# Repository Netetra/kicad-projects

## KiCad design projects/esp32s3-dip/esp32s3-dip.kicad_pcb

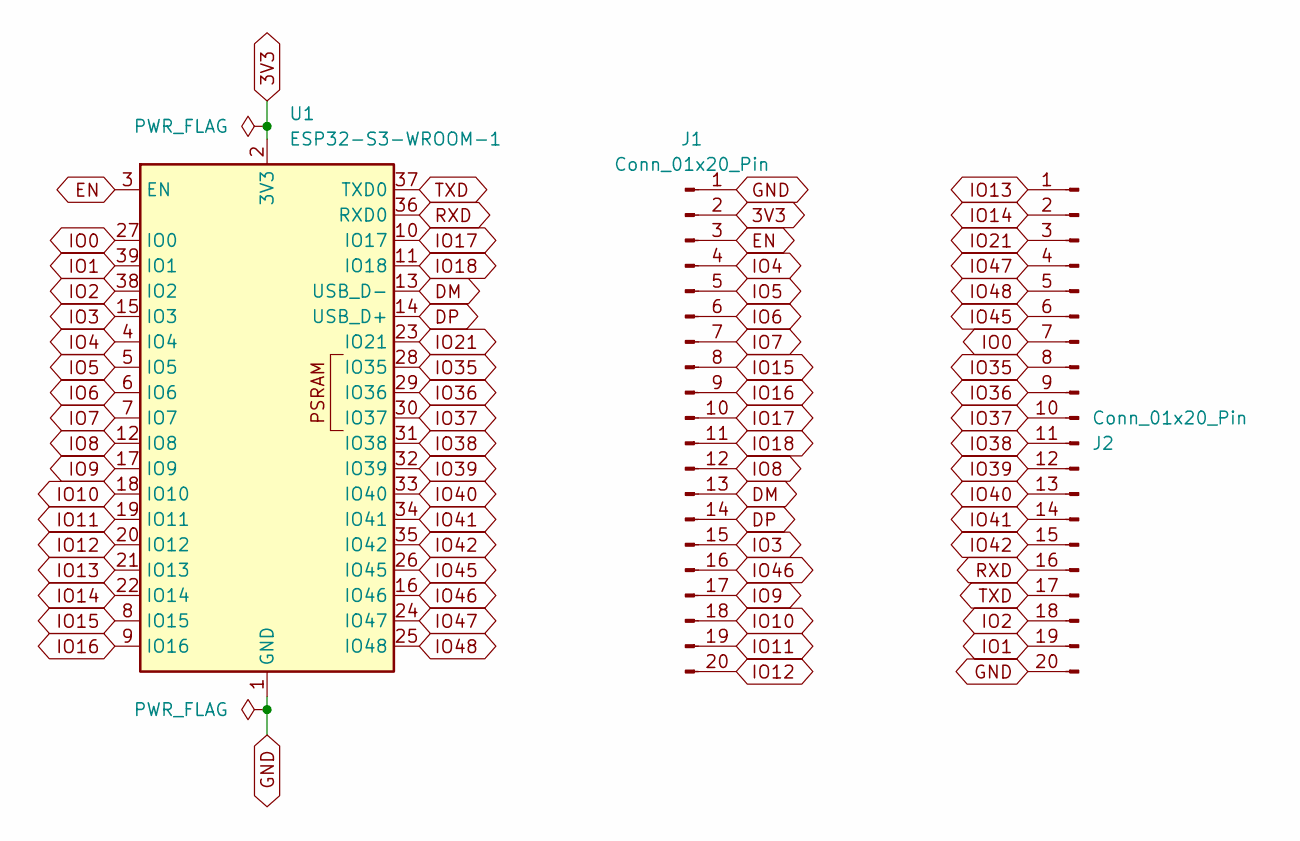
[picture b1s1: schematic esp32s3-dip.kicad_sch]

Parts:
J1, J2: Conn_01x20_Pin; PinHeader_1x20_P2.54mm_Vertical
U1: ESP32-S3-WROOM-1; ESP32-S3-WROOM-1U

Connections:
3V3: J1.2, U1.2 (3V3)
DM: J1.13, U1.13 (USB_D-)
DP: J1.14, U1.14 (USB_D+)
EN: J1.3, U1.3 (EN)
GND: J1.1, J2.20, U1.1 (GND), U1.40 (GND), U1.41 (GND)
IO0: J2.7, U1.27 (IO0)
IO1: J2.19, U1.39 (IO1)
IO2: J2.18, U1.38 (IO2)
IO3: J1.15, U1.15 (IO3)
IO4: J1.4, U1.4 (IO4)
IO5: J1.5, U1.5 (IO5)
IO6: J1.6, U1.6 (IO6)
IO7: J1.7, U1.7 (IO7)
IO8: J1.12, U1.12 (IO8)
IO9: J1.17, U1.17 (IO9)
IO10: J1.18, U1.18 (IO10)
IO11: J1.19, U1.19 (IO11)
IO12: J1.20, U1.20 (IO12)
IO13: J2.1, U1.21 (IO13)
IO14: J2.2, U1.22 (IO14)
IO15: J1.8, U1.8 (IO15)
IO16: J1.9, U1.9 (IO16)
IO17: J1.10, U1.10 (IO17)
IO18: J1.11, U1.11 (IO18)
IO21: J2.3, U1.23 (IO21)
IO35: J2.8, U1.28 (IO35)
IO36: J2.9, U1.29 (IO36)
IO37: J2.10, U1.30 (IO37)
IO38: J2.11, U1.31 (IO38)
IO39: J2.12, U1.32 (IO39)
IO40: J2.13, U1.33 (IO40)
IO41: J2.14, U1.34 (IO41)
IO42: J2.15, U1.35 (IO42)
IO45: J2.6, U1.26 (IO45)
IO46: J1.16, U1.16 (IO46)
IO47: J2.4, U1.24 (IO47)
IO48: J2.5, U1.25 (IO48)
RXD: J2.16, U1.36 (RXD0)
TXD: J2.17, U1.37 (TXD0)

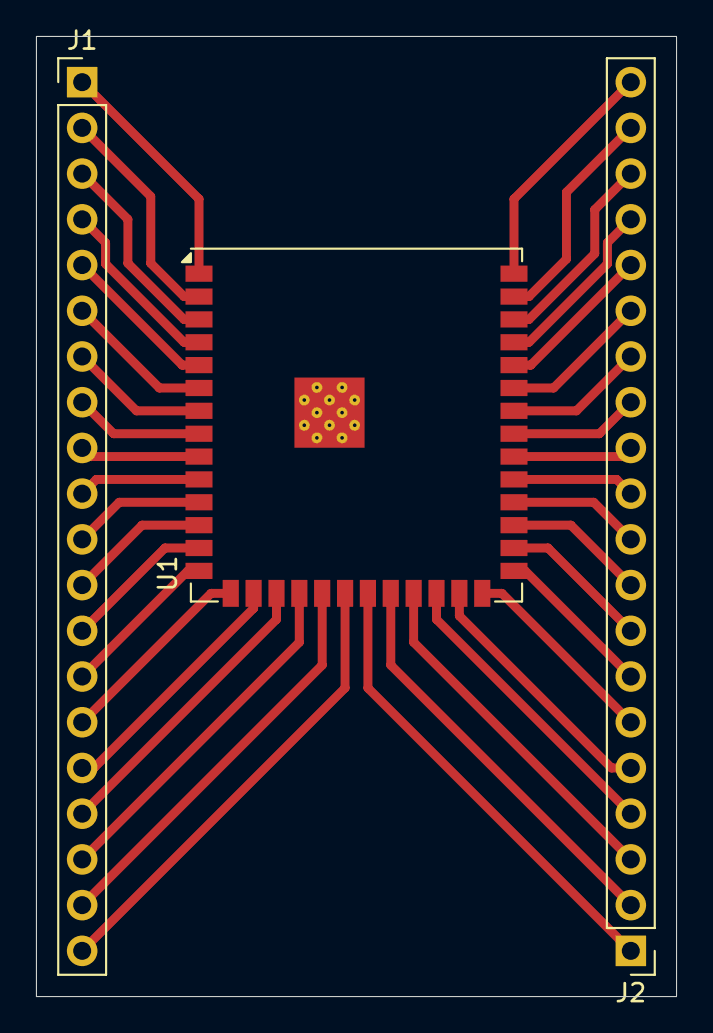
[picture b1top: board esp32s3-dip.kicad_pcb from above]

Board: 2 copper layers, 35.6 x 53.3 mm, 3 parts (0 on the bottom side), 39 nets.

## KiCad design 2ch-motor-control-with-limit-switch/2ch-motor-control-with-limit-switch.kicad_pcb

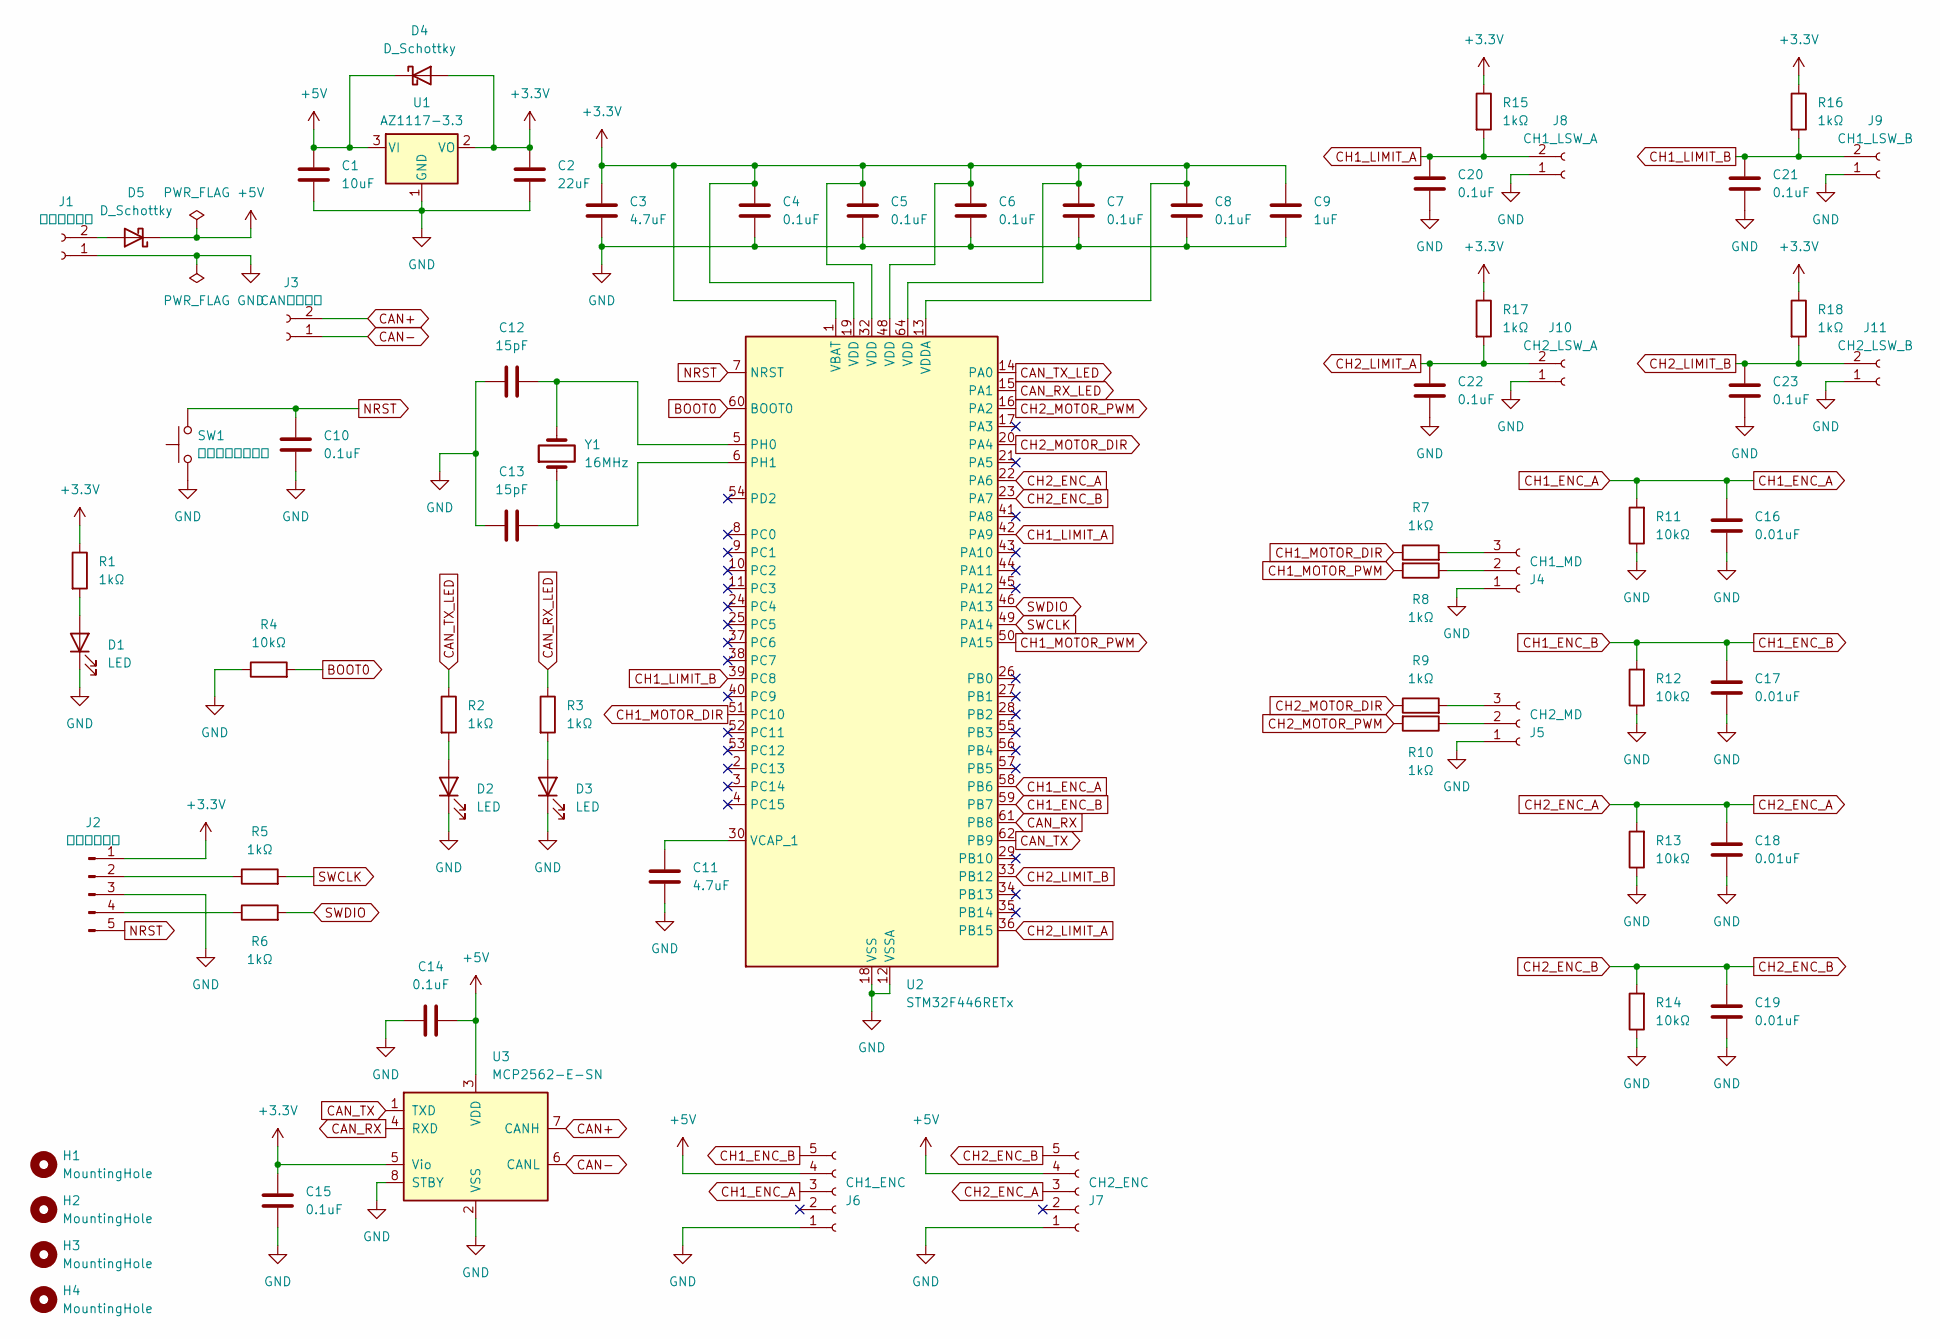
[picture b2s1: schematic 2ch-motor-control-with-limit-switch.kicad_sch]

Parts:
C1: 10uF; C_0603_1608Metric
C2: 22uF; C_0603_1608Metric
C3, C11: 4.7uF; C_0603_1608Metric
C4, C5, C6, C7, C8, C10, C14, C15, C20, C21, C22, C23: 0.1uF; C_0603_1608Metric
C9: 1uF; C_0603_1608Metric
C12, C13: 15pF; C_0603_1608Metric
C16, C17, C18, C19: 0.01uF; C_0603_1608Metric
D1, D2, D3: LED; LED_0603_1608Metric
D4, D5: D_Schottky; US2H
H1, H2, H3, H4: MountingHole; MountingHole_3.2mm_M3
J1: 電源コネクタ; AMASS_XT30PW-M_1x02_P2.50mm_Horizontal
J2: デバッグ端子; PinSocket_1x05_P2.54mm_Horizontal
J3: CANコネクタ; JST_XH_S2B-XH-A_1x02_P2.50mm_Horizontal
J4: CH1_MD; JST_XH_S3B-XH-A_1x03_P2.50mm_Horizontal
J5: CH2_MD; JST_XH_S3B-XH-A_1x03_P2.50mm_Horizontal
J6: CH1_ENC; JST_XH_S5B-XH-A_1x05_P2.50mm_Horizontal
J7: CH2_ENC; JST_XH_S5B-XH-A_1x05_P2.50mm_Horizontal
J8: CH1_LSW_A; JST_XH_S2B-XH-A_1x02_P2.50mm_Horizontal
J9: CH1_LSW_B; JST_XH_S2B-XH-A_1x02_P2.50mm_Horizontal
J10: CH2_LSW_A; JST_XH_S2B-XH-A_1x02_P2.50mm_Horizontal
J11: CH2_LSW_B; JST_XH_S2B-XH-A_1x02_P2.50mm_Horizontal
R1, R2, R3, R5, R6, R7, R8, R9, R10, R15, R16, R17, R18: 1kΩ; R_0603_1608Metric
R4, R11, R12, R13, R14: 10kΩ; R_0603_1608Metric
SW1: リセットスイッチ; SW_PUSH_6mm_H5mm
U1: AZ1117-3.3; SOT-223-3_TabPin2
U2: STM32F446RETx; LQFP-64_10x10mm_P0.5mm
U3: MCP2562-E-SN; SOIC-8_3.9x4.9mm_P1.27mm
Y1: 16MHz; Crystal_HC49-4H_Vertical

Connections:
+3.3V: C2.1, C3.1, C4.1, C5.1, C6.1, C7.1, C8.1, C9.1, C15.1, D4.2 (A), J2.1, R1.1, R15.1, R16.1, R17.1, R18.1, U1.2 (VO), U2.1 (VBAT), U2.13 (VDDA), U2.19 (VDD), U2.32 (VDD), U2.48 (VDD), U2.64 (VDD), U3.5 (Vio)
+5V: C1.1, C14.2, D4.1 (K), D5.1 (K), J6.4, J7.4, U1.3 (VI), U3.3 (VDD)
BOOT0: R4.2, U2.60 (BOOT0)
CAN+: J3.2, U3.7 (CANH)
CAN-: J3.1, U3.6 (CANL)
CAN_RX: U2.61 (PB8), U3.4 (RXD)
CAN_RX_LED: R3.1, U2.15 (PA1)
CAN_TX: U2.62 (PB9), U3.1 (TXD)
CAN_TX_LED: R2.1, U2.14 (PA0)
CH1_ENC_A: C16.1, J6.3, R11.2, U2.58 (PB6)
CH1_ENC_B: C17.1, J6.5, R12.2, U2.59 (PB7)
CH1_LIMIT_A: C20.1, J8.2, R15.2, U2.42 (PA9)
CH1_LIMIT_B: C21.1, J9.2, R16.2, U2.39 (PC8)
CH1_MOTOR_DIR: R7.1, U2.51 (PC10)
CH1_MOTOR_PWM: R8.2, U2.50 (PA15)
CH2_ENC_A: C18.1, J7.3, R13.2, U2.22 (PA6)
CH2_ENC_B: C19.1, J7.5, R14.2, U2.23 (PA7)
CH2_LIMIT_A: C22.1, J10.2, R17.2, U2.36 (PB15)
CH2_LIMIT_B: C23.1, J11.2, R18.2, U2.33 (PB12)
CH2_MOTOR_DIR: R9.1, U2.20 (PA4)
CH2_MOTOR_PWM: R10.2, U2.16 (PA2)
GND: C1.2, C2.2, C3.2, C4.2, C5.2, C6.2, C7.2, C8.2, C9.2, C10.2, C11.1, C12.1, C13.1, C14.1, C15.2, C16.2, C17.2, C18.2, C19.2, C20.2, C21.2, C22.2, C23.2, D1.1 (K), D2.1 (K), D3.1 (K), J1.1, J2.3, J4.1, J5.1, J6.1, J7.1, J8.1, J9.1, J10.1, J11.1, R4.1, R11.1, R12.1, R13.1, R14.1, SW1.1, U1.1 (GND), U2.12 (VSSA), U2.18 (VSS), U2.31 (VSS), U2.47 (VSS), U2.63 (VSS), U3.2 (VSS), U3.8 (STBY)
NRST: C10.1, J2.5, SW1.2, U2.7 (NRST)
unnamed: D1.2 (A), R1.2
unnamed: D2.2 (A), R2.2
unnamed: D3.2 (A), R3.2
unnamed: D5.2 (A), J1.2
unnamed: J2.2, R5.1
unnamed: J2.4, R6.1
unnamed: J4.2, R8.1
unnamed: J4.3, R7.2
unnamed: J5.2, R10.1
unnamed: J5.3, R9.2
unnamed: C12.2, U2.5 (PH0), Y1.2
unnamed: C13.2, U2.6 (PH1), Y1.1
unnamed: C11.2, U2.30 (VCAP_1)
SWCLK: R5.2, U2.49 (PA14)
SWDIO: R6.2, U2.46 (PA13)

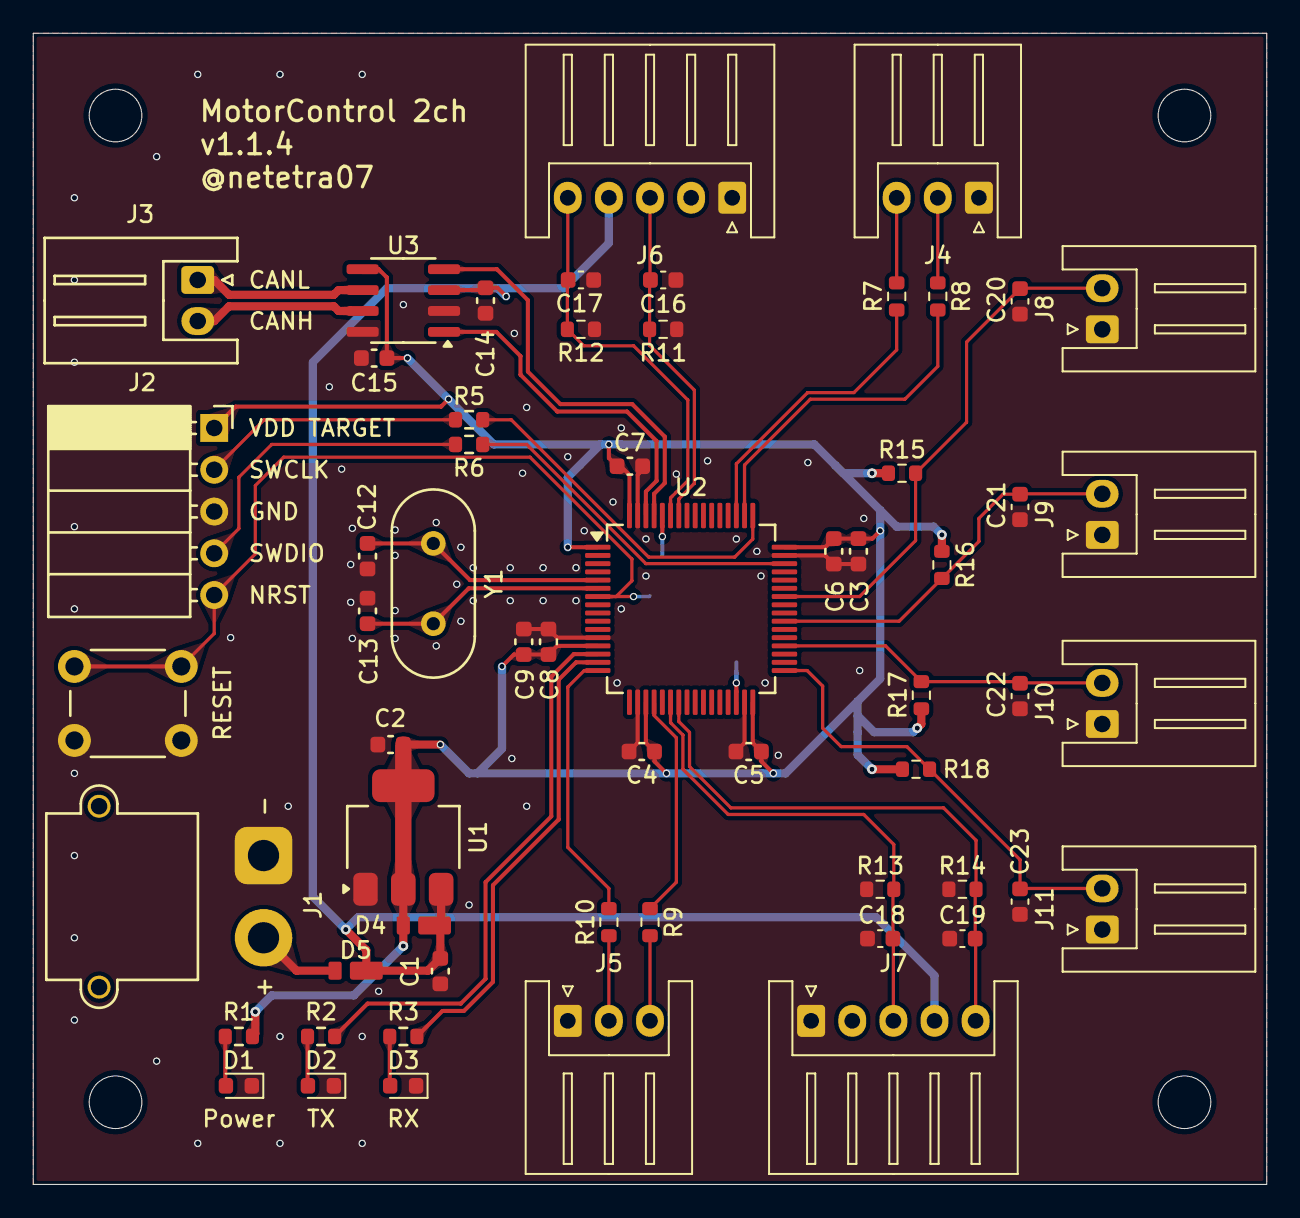
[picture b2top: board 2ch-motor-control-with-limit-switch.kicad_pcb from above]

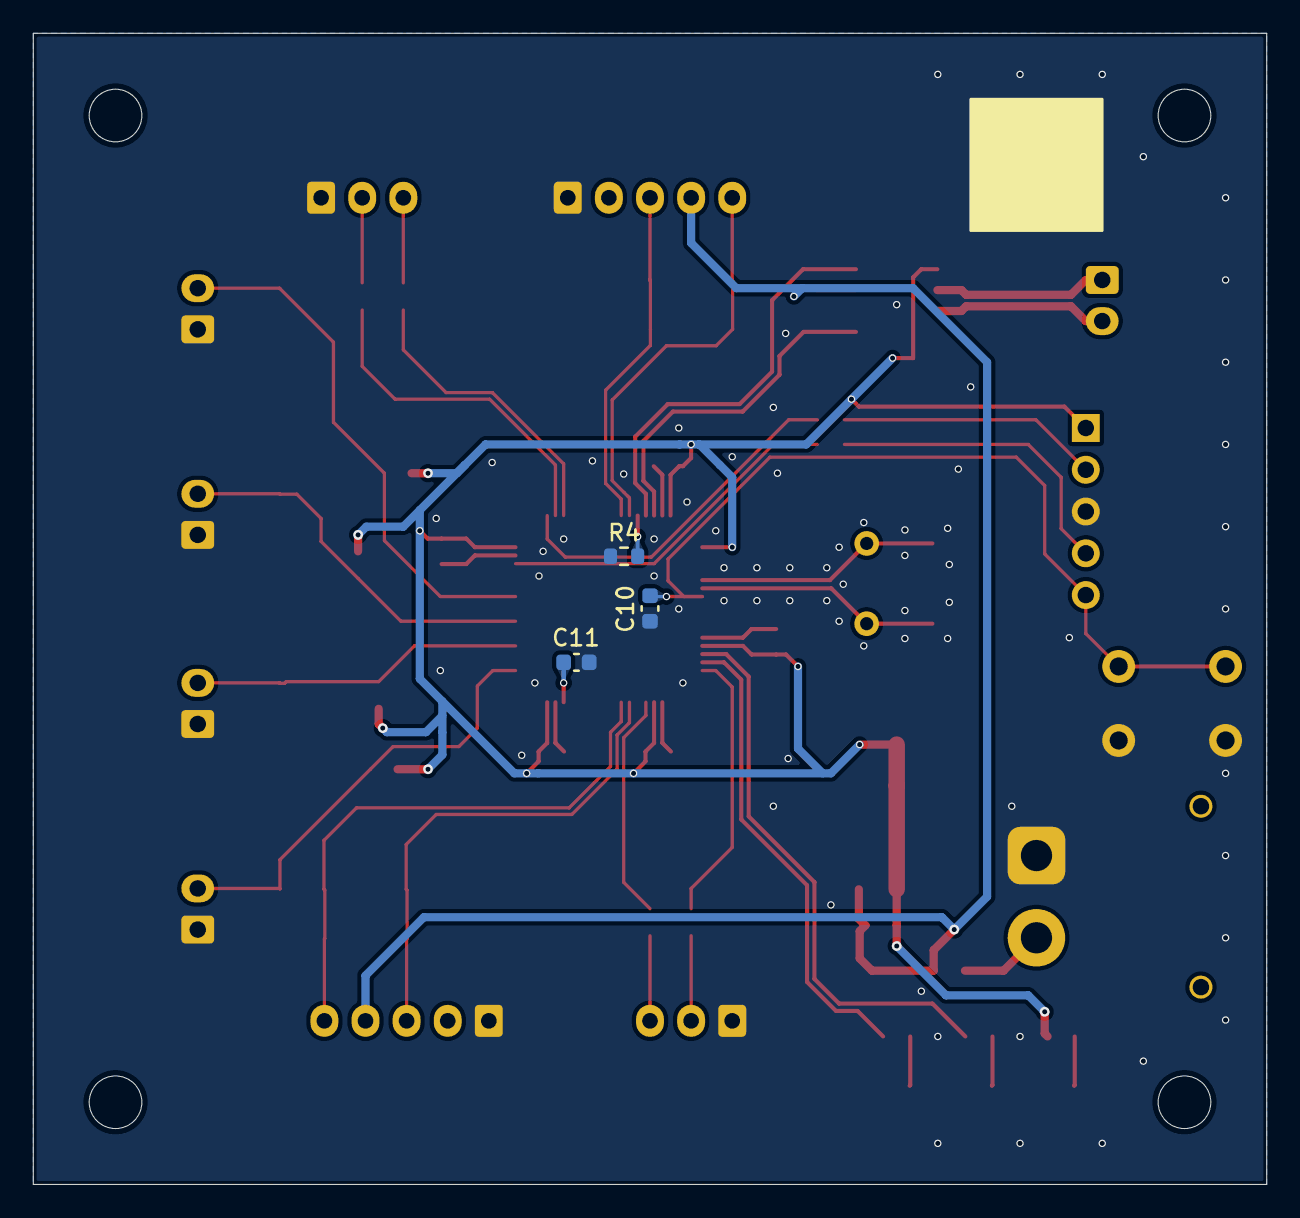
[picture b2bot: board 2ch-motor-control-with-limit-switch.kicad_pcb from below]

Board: 2 copper layers, 75.0 x 70.0 mm, 66 parts (3 on the bottom side), 38 nets.

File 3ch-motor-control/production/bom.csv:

Designator,Footprint,Quantity,Value,LCSC Part #
C1,0603,1,10uF,
"C10, C14, C15, C4, C5, C6, C7, C8",0603,8,0.1uF,
"C11, C3",0603,2,4.7uF,
"C12, C13",0603,2,15pF,
"C16, C17, C18, C19, C20, C21",0603,6,0.01uF,
C2,0603,1,22uF,
C9,0603,1,1uF,
"D1, D2, D3",0603,3,LED,
ENC1,JST_XH_S5B-XH-A_1x05_P2.50mm_Horizontal,1,CH1_ENC,
ENC2,JST_XH_S5B-XH-A_1x05_P2.50mm_Horizontal,1,CH2_ENC,
ENC3,JST_XH_S5B-XH-A_1x05_P2.50mm_Horizontal,1,CH3_ENC,
J1,AMASS_XT30PW-M_1x02_P2.50mm_Horizontal,1,電源コネクタ,
J2,PinSocket_1x05_P2.54mm_Horizontal,1,デバッグ端子,
J3,JST_XH_S2B-XH-A_1x02_P2.50mm_Horizontal,1,CANコネクタ,
MD1,JST_XH_S3B-XH-A_1x03_P2.50mm_Horizontal,1,CH1_MOTOR,
MD2,JST_XH_S3B-XH-A_1x03_P2.50mm_Horizontal,1,CH2_MOTOR,
MD3,JST_XH_S3B-XH-A_1x03_P2.50mm_Horizontal,1,CH3_MOTOR,
"R1, R10, R11, R12, R14, R16, R17, R18, R2, R20, R22, R23, R24, R3, R5, R6, R8",0603,17,1kΩ,
"R13, R15, R19, R21, R4, R7, R9",0603,7,10kΩ,
SW1,SW_PUSH_6mm_H5mm,1,リセットスイッチ,
U1,SOT-223-3_TabPin2,1,AZ1117-3.3,
U2,LQFP-64_10x10mm_P0.5mm,1,STM32F446RETx,
U3,SOIC-8_3.9x4.9mm_P1.27mm,1,MCP2562-E-SN,
Y1,Crystal_HC49-4H_Vertical,1,16MHz,

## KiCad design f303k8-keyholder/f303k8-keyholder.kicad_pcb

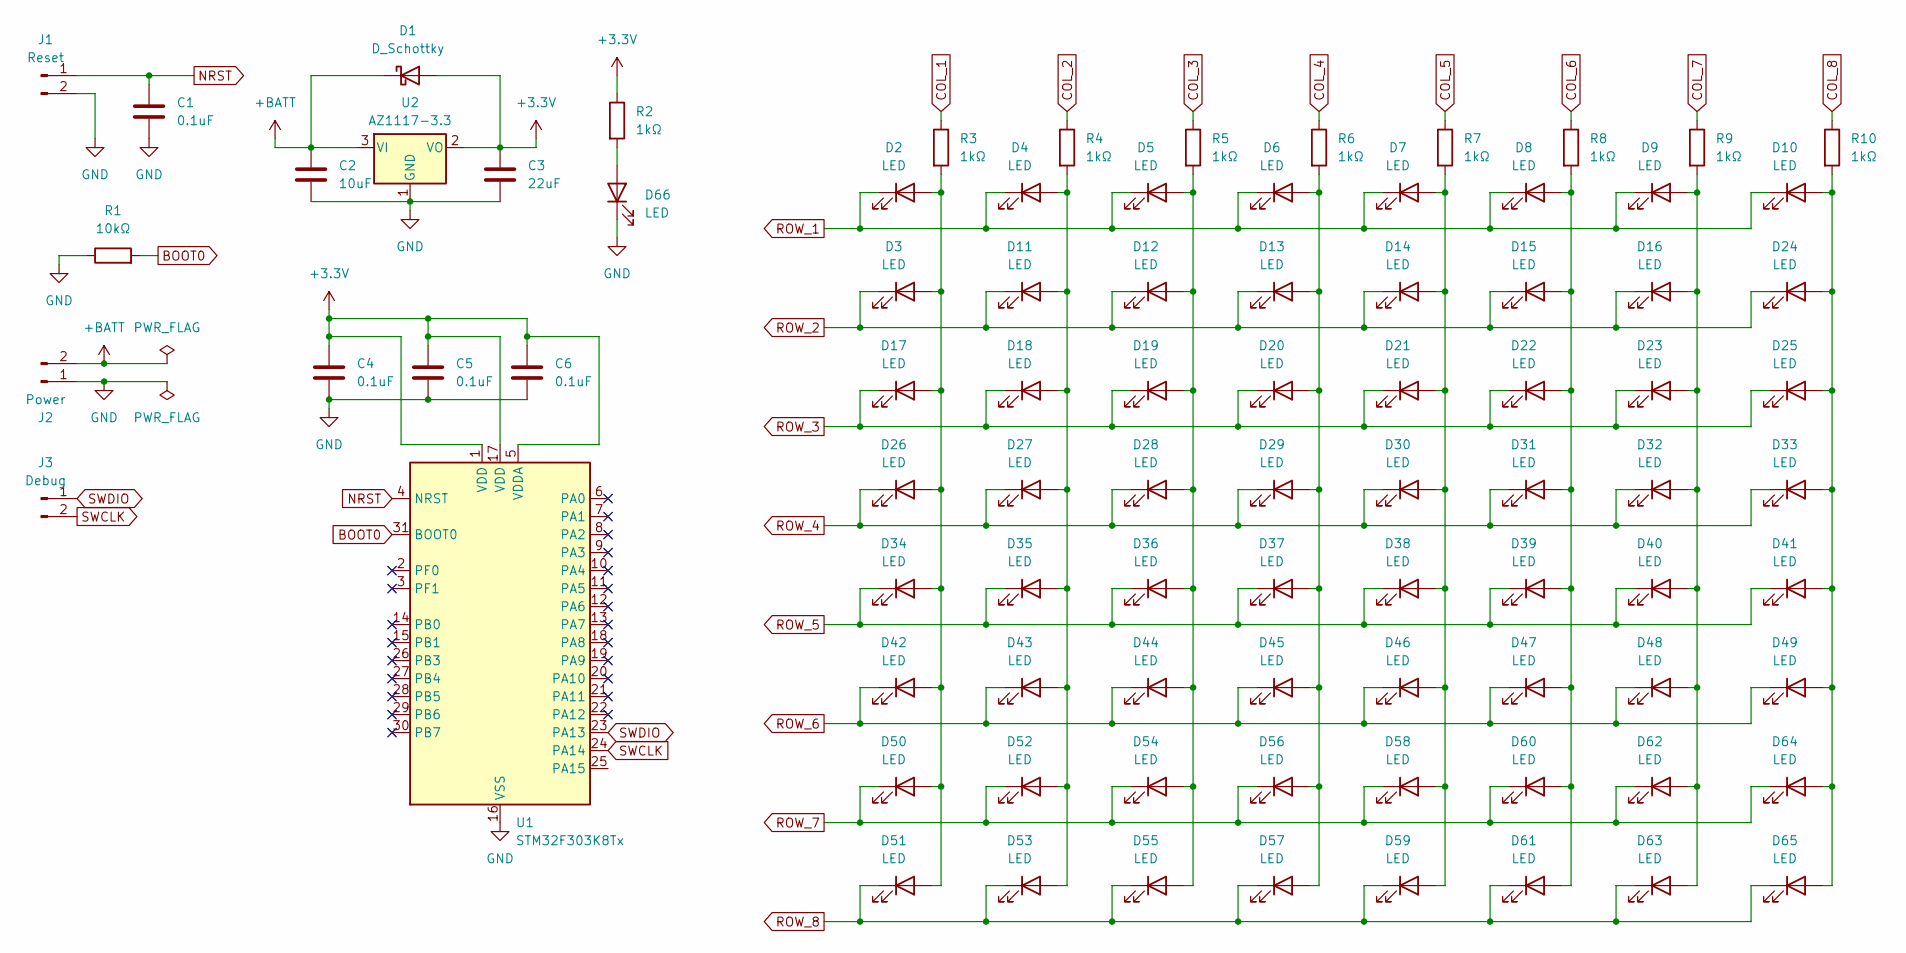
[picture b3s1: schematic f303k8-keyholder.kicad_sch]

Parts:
C1, C4, C5, C6: 0.1uF; C_0603_1608Metric
C2: 10uF; C_0603_1608Metric
C3: 22uF; C_0603_1608Metric
D1: D_Schottky; US2H
D2, D3, D4, D5, D6, D7, D8, D9, D10, D11, D12, D13, D14, D15, D16, D17, D18, D19, D20, D21, D22, D23, D24, D25, D26, D27, D28, D29, D30, D31, D32, D33, D34, D35, D36, D37, D38, D39, D40, D41, D42, D43, D44, D45, D46, D47, D48, D49, D50, D51, D52, D53, D54, D55, D56, D57, D58, D59, D60, D61, D62, D63, D64, D65, D66: LED; LED_0603_1608Metric
J1: Reset; PinHeader_1x02_P1.00mm_Vertical
J2: Power; PinSocket_1x02_P2.54mm_Horizontal
J3: Debug; PinHeader_1x02_P1.00mm_Vertical
R1: 10kΩ; R_0603_1608Metric
R2, R3, R4, R5, R6, R7, R8, R9, R10: 1kΩ; R_0603_1608Metric
U1: STM32F303K8Tx; LQFP-32_7x7mm_P0.8mm
U2: AZ1117-3.3; SOT-223-3_TabPin2

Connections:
+3.3V: C3.1, C4.1, C5.1, C6.1, D1.2 (A), R2.1, U1.1 (VDD), U1.5 (VDDA), U1.17 (VDD), U2.2 (VO)
+BATT: C2.1, D1.1 (K), J2.2, U2.3 (VI)
BOOT0: R1.2, U1.31 (BOOT0)
COL_1: R3.1
COL_2: R4.1
COL_3: R5.1
COL_4: R6.1
COL_5: R7.1
COL_6: R8.1
COL_7: R9.1
COL_8: R10.1
GND: C1.2, C2.2, C3.2, C4.2, C5.2, C6.2, D66.1 (K), J1.2, J2.1, R1.1, U1.16 (VSS), U1.32 (VSS), U2.1 (GND)
NRST: C1.1, J1.1, U1.4 (NRST)
unnamed: D10.2 (A), D24.2 (A), D25.2 (A), D33.2 (A), D41.2 (A), D49.2 (A), D64.2 (A), D65.2 (A), R10.2
unnamed: D4.2 (A), D11.2 (A), D18.2 (A), D27.2 (A), D35.2 (A), D43.2 (A), D52.2 (A), D53.2 (A), R4.2
unnamed: D5.2 (A), D12.2 (A), D19.2 (A), D28.2 (A), D36.2 (A), D44.2 (A), D54.2 (A), D55.2 (A), R5.2
unnamed: D6.2 (A), D13.2 (A), D20.2 (A), D29.2 (A), D37.2 (A), D45.2 (A), D56.2 (A), D57.2 (A), R6.2
unnamed: D7.2 (A), D14.2 (A), D21.2 (A), D30.2 (A), D38.2 (A), D46.2 (A), D58.2 (A), D59.2 (A), R7.2
unnamed: D8.2 (A), D15.2 (A), D22.2 (A), D31.2 (A), D39.2 (A), D47.2 (A), D60.2 (A), D61.2 (A), R8.2
unnamed: D9.2 (A), D16.2 (A), D23.2 (A), D32.2 (A), D40.2 (A), D48.2 (A), D62.2 (A), D63.2 (A), R9.2
unnamed: D2.2 (A), D3.2 (A), D17.2 (A), D26.2 (A), D34.2 (A), D42.2 (A), D50.2 (A), D51.2 (A), R3.2
unnamed: D66.2 (A), R2.2
ROW_1: D2.1 (K), D4.1 (K), D5.1 (K), D6.1 (K), D7.1 (K), D8.1 (K), D9.1 (K), D10.1 (K)
ROW_2: D3.1 (K), D11.1 (K), D12.1 (K), D13.1 (K), D14.1 (K), D15.1 (K), D16.1 (K), D24.1 (K)
ROW_3: D17.1 (K), D18.1 (K), D19.1 (K), D20.1 (K), D21.1 (K), D22.1 (K), D23.1 (K), D25.1 (K)
ROW_4: D26.1 (K), D27.1 (K), D28.1 (K), D29.1 (K), D30.1 (K), D31.1 (K), D32.1 (K), D33.1 (K)
ROW_5: D34.1 (K), D35.1 (K), D36.1 (K), D37.1 (K), D38.1 (K), D39.1 (K), D40.1 (K), D41.1 (K)
ROW_6: D42.1 (K), D43.1 (K), D44.1 (K), D45.1 (K), D46.1 (K), D47.1 (K), D48.1 (K), D49.1 (K)
ROW_7: D50.1 (K), D52.1 (K), D54.1 (K), D56.1 (K), D58.1 (K), D60.1 (K), D62.1 (K), D64.1 (K)
ROW_8: D51.1 (K), D53.1 (K), D55.1 (K), D57.1 (K), D59.1 (K), D61.1 (K), D63.1 (K), D65.1 (K)
SWCLK: J3.2, U1.24 (PA14)
SWDIO: J3.1, U1.23 (PA13)

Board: 2 copper layers, 87 parts (0 on the bottom side), 24 nets, no tracks yet.

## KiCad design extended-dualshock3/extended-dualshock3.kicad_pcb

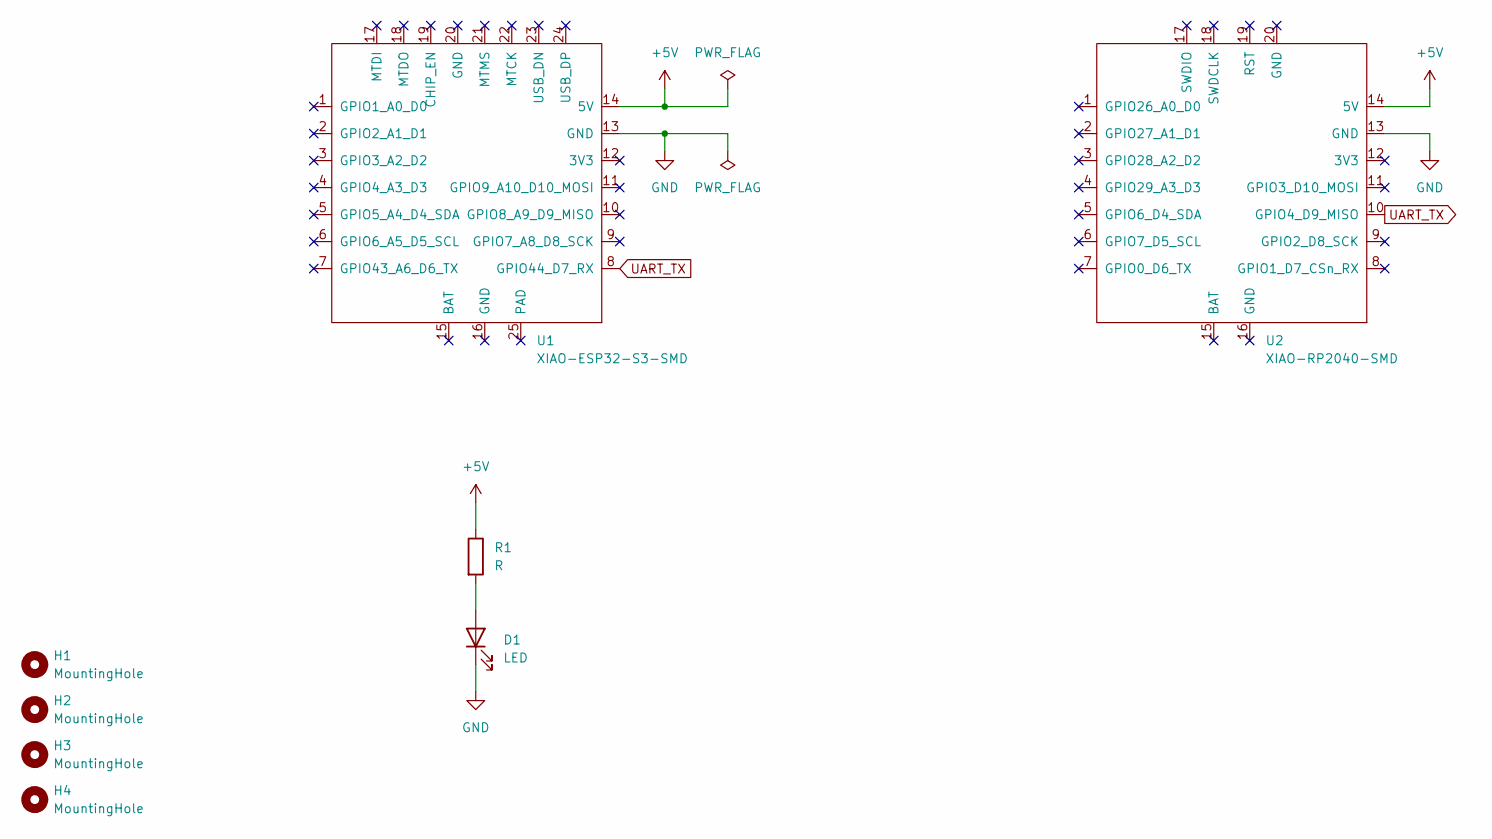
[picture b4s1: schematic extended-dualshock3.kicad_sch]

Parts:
D1: LED; LED_0603_1608Metric
H1, H2, H3, H4: MountingHole; MountingHole_3.2mm_M3
R1: R; R_0603_1608Metric
U1: XIAO-ESP32-S3-SMD; XIAO-ESP32S3-SMD
U2: XIAO-RP2040-SMD

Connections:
+5V: R1.1, U1.14 (5V), U2.14 (5V)
GND: D1.1 (K), U1.13 (GND), U2.13 (GND)
unnamed: D1.2 (A), R1.2
UART_TX: U1.8 (GPIO44_D7_RX), U2.10 (GPIO4_D9_MISO)

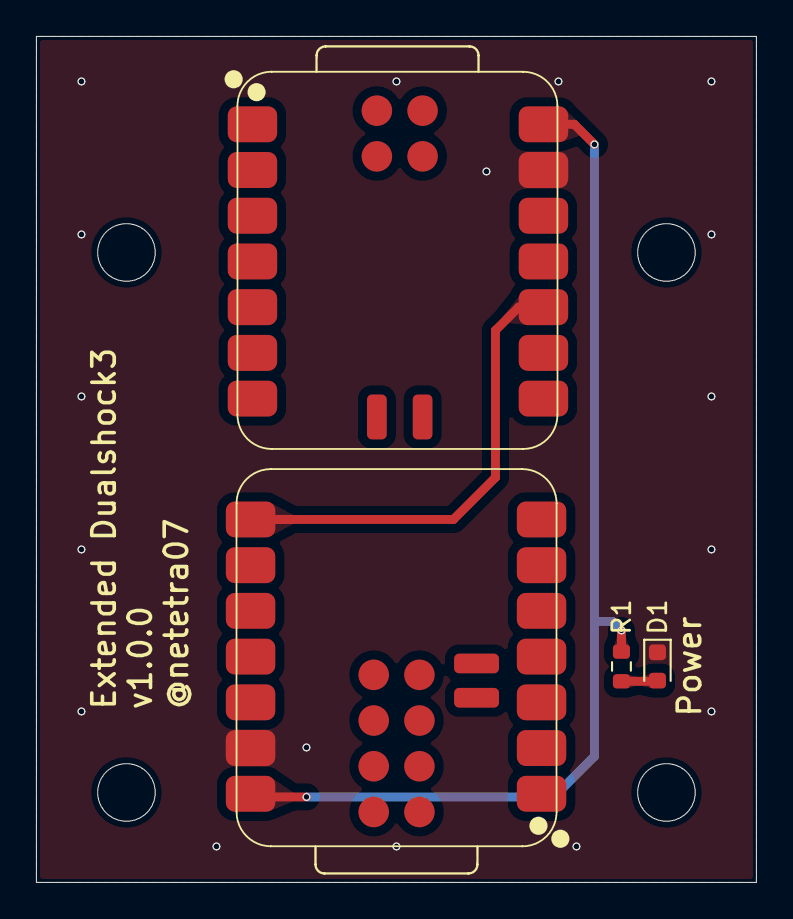
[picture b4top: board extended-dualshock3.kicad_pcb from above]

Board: 2 copper layers, 40.0 x 47.0 mm, 8 parts (0 on the bottom side), 4 nets.

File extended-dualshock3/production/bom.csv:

Designator,Footprint,Quantity,Value,LCSC Part #
D1,0603,1,LED,
R1,0603,1,R,
U1,XIAO-ESP32S3-SMD,1,XIAO-ESP32-S3-SMD,
U2,XIAO-RP2040-SMD,1,XIAO-RP2040-SMD,

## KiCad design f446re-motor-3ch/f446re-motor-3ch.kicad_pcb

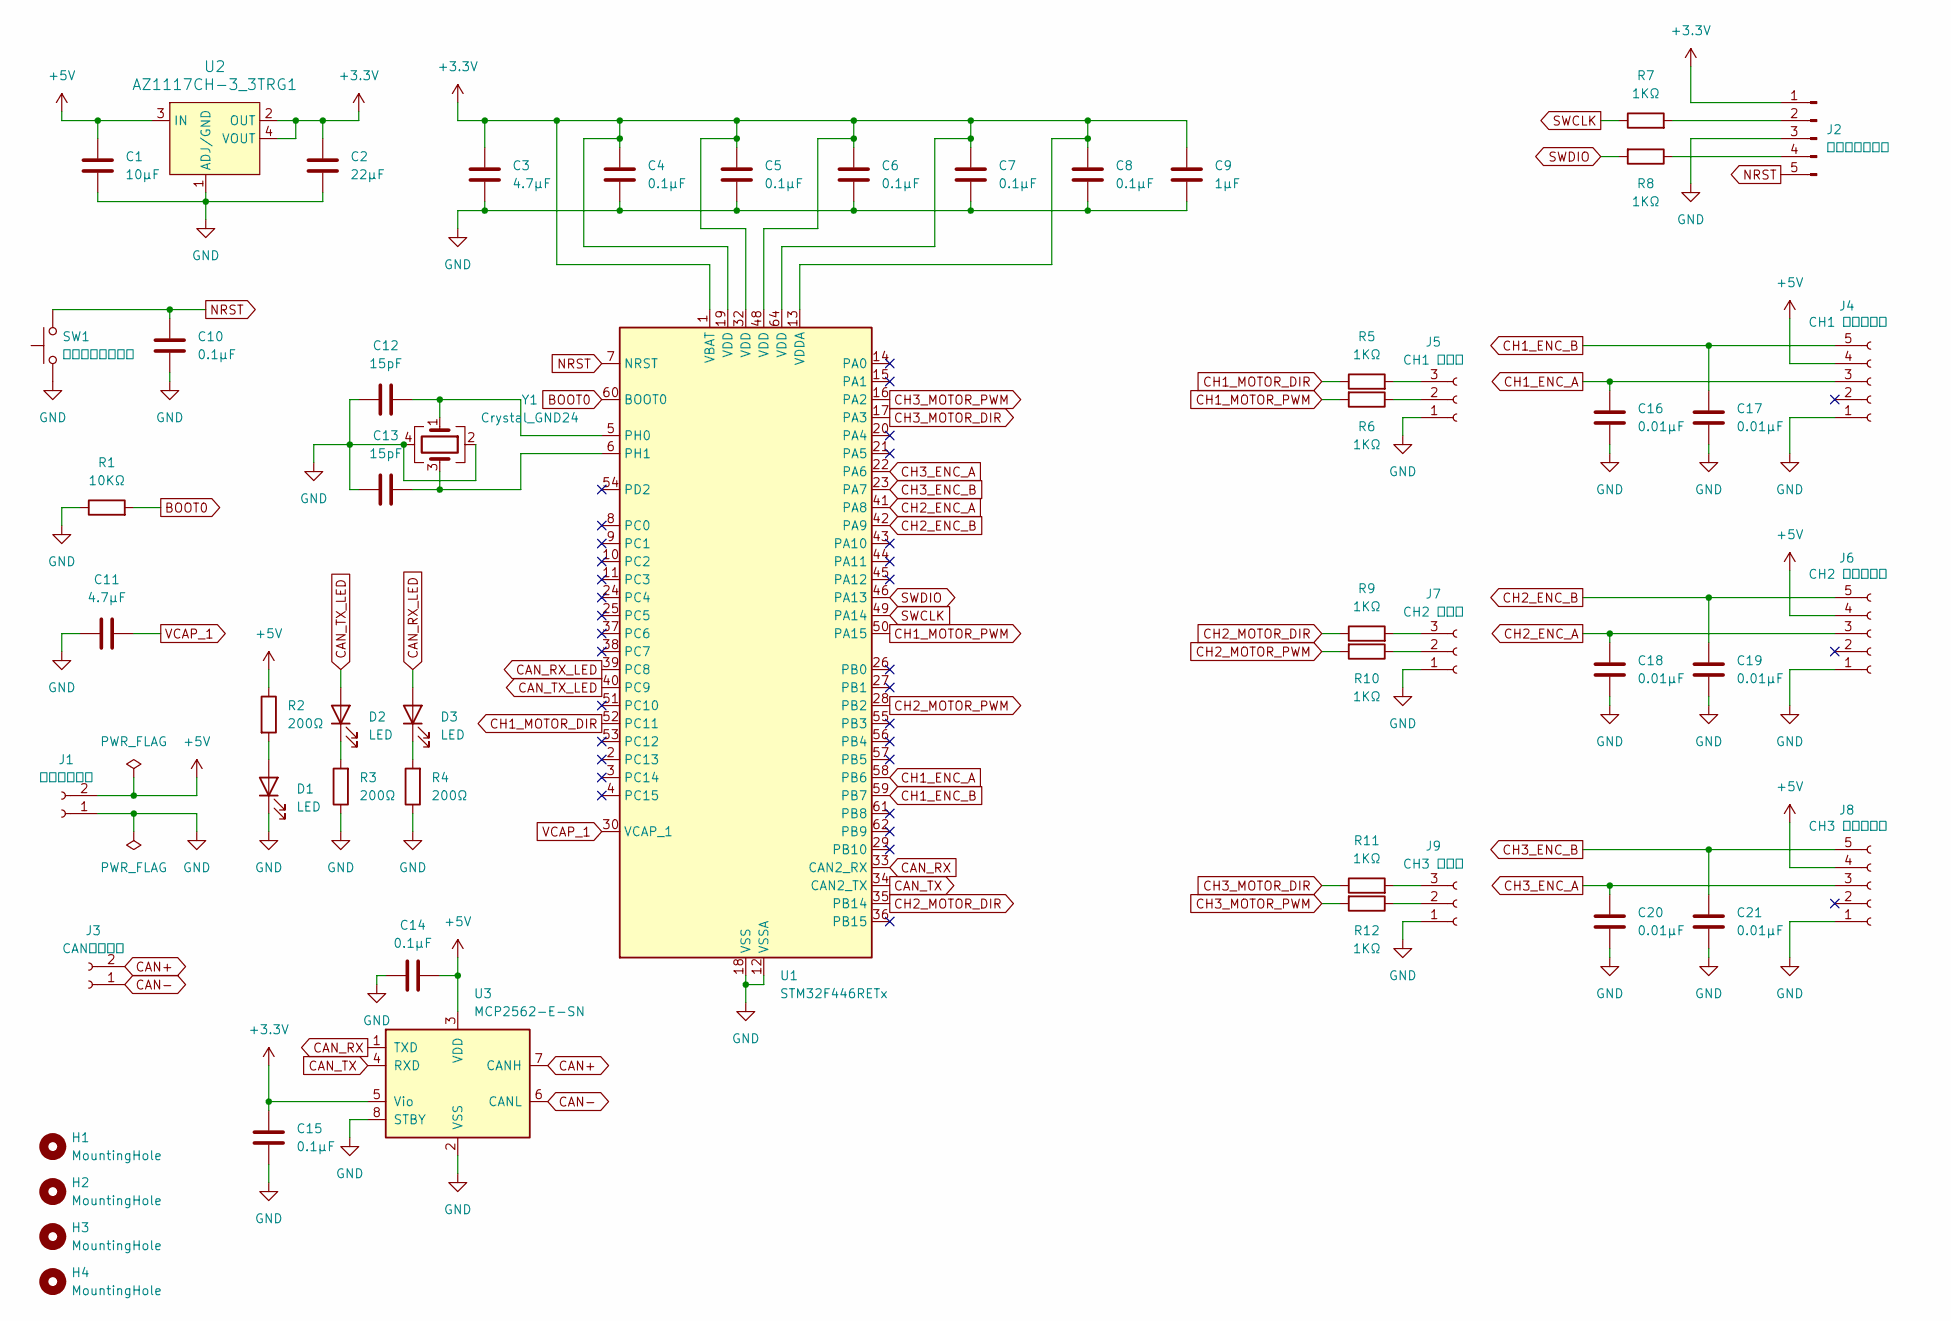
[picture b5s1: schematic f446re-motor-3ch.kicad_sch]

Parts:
C1: 10μF; C_0603_1608Metric
C2: 22μF; C_0603_1608Metric
C3, C11: 4.7μF; C_0603_1608Metric
C4, C5, C6, C7, C8, C10, C14, C15: 0.1μF; C_0603_1608Metric
C9: 1μF; C_0603_1608Metric
C12, C13: 15pF; C_0603_1608Metric
C16, C17, C18, C19, C20, C21: 0.01μF; C_0603_1608Metric
D1, D2, D3: LED; LED_0603_1608Metric
H1, H2, H3, H4: MountingHole; MountingHole_3.2mm_M3
J1: 電源コネクタ; AMASS_XT30PW-M_1x02_P2.50mm_Horizontal
J2: デバッグ用端子; PinSocket_1x05_P2.54mm_Horizontal
J3: CANコネクタ; JST_XH_S2B-XH-A_1x02_P2.50mm_Horizontal
J4: CH1 エンコーダ; JST_XH_S5B-XH-A_1x05_P2.50mm_Horizontal
J5: CH1 モータ; JST_XH_S3B-XH-A_1x03_P2.50mm_Horizontal
J6: CH2 エンコーダ; JST_XH_S5B-XH-A_1x05_P2.50mm_Horizontal
J7: CH2 モータ; JST_XH_S3B-XH-A_1x03_P2.50mm_Horizontal
J8: CH3 エンコーダ; JST_XH_S5B-XH-A_1x05_P2.50mm_Horizontal
J9: CH3 モータ; JST_XH_S3B-XH-A_1x03_P2.50mm_Horizontal
R1: 10KΩ; R_0603_1608Metric
R2, R3, R4: 200Ω; R_0603_1608Metric
R5, R6, R7, R8, R9, R10, R11, R12: 1KΩ; R_0603_1608Metric
SW1: リセットスイッチ; SW_PUSH_6mm_H5mm
U1: STM32F446RETx; LQFP-64_10x10mm_P0.5mm
U2: AZ1117CH-3_3TRG1; SOT-223; MPN AZ1117CH-3.3TRG1; Digi-Key_PN AZ1117CH-3.3TRG1DICT-ND
U3: MCP2562-E-SN; SOIC-8_3.9x4.9mm_P1.27mm
Y1: Crystal_GND24; Crystal_SMD_SeikoEpson_FA238-4Pin_3.2x2.5mm_HandSoldering

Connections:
+3.3V: C2.1, C3.1, C4.1, C5.1, C6.1, C7.1, C8.1, C9.1, C15.2, J2.1, U1.1 (VBAT), U1.13 (VDDA), U1.19 (VDD), U1.32 (VDD), U1.48 (VDD), U1.64 (VDD), U2.2 (OUT), U2.4 (VOUT), U3.5 (Vio)
+5V: C1.1, C14.1, J1.2, J4.4, J6.4, J8.4, R2.1, U2.3 (IN), U3.3 (VDD)
BOOT0: R1.2, U1.60 (BOOT0)
CAN+: J3.2, U3.7 (CANH)
CAN-: J3.1, U3.6 (CANL)
CAN_RX: U1.33 (CAN2_RX), U3.1 (TXD)
CAN_RX_LED: D3.2 (A), U1.39 (PC8)
CAN_TX: U1.34 (CAN2_TX), U3.4 (RXD)
CAN_TX_LED: D2.2 (A), U1.40 (PC9)
CH1_ENC_A: C16.1, J4.3, U1.58 (PB6)
CH1_ENC_B: C17.1, J4.5, U1.59 (PB7)
CH1_MOTOR_DIR: R5.1, U1.52 (PC11)
CH1_MOTOR_PWM: R6.2, U1.50 (PA15)
CH2_ENC_A: C18.1, J6.3, U1.41 (PA8)
CH2_ENC_B: C19.1, J6.5, U1.42 (PA9)
CH2_MOTOR_DIR: R9.1, U1.35 (PB14)
CH2_MOTOR_PWM: R10.2, U1.28 (PB2)
CH3_ENC_A: C20.1, J8.3, U1.22 (PA6)
CH3_ENC_B: C21.1, J8.5, U1.23 (PA7)
CH3_MOTOR_DIR: R11.1, U1.17 (PA3)
CH3_MOTOR_PWM: R12.2, U1.16 (PA2)
GND: C1.2, C2.2, C3.2, C4.2, C5.2, C6.2, C7.2, C8.2, C9.2, C10.2, C11.1, C12.1, C13.1, C14.2, C15.1, C16.2, C17.2, C18.2, C19.2, C20.2, C21.2, D1.1 (K), J1.1, J2.3, J4.1, J5.1, J6.1, J7.1, J8.1, J9.1, R1.1, R3.1, R4.1, SW1.1, U1.12 (VSSA), U1.18 (VSS), U1.31 (VSS), U1.47 (VSS), U1.63 (VSS), U2.1 (ADJ/GND), U3.2 (VSS), U3.8 (STBY), Y1.2, Y1.4
NRST: C10.1, J2.5, SW1.2, U1.7 (NRST)
unnamed: D1.2 (A), R2.2
unnamed: D2.1 (K), R3.2
unnamed: D3.1 (K), R4.2
unnamed: J2.2, R7.2
unnamed: J2.4, R8.1
unnamed: J5.2, R6.1
unnamed: J5.3, R5.2
unnamed: J7.2, R10.1
unnamed: J7.3, R9.2
unnamed: J9.2, R12.1
unnamed: J9.3, R11.2
unnamed: C12.2, U1.5 (PH0), Y1.1
unnamed: C13.2, U1.6 (PH1), Y1.3
SWCLK: R7.1, U1.49 (PA14)
SWDIO: R8.2, U1.46 (PA13)
VCAP_1: C11.2, U1.30 (VCAP_1)
